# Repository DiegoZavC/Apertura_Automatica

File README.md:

# Apertura_Automatica
 Desarrollo de un sistema de apertura automática para una puera

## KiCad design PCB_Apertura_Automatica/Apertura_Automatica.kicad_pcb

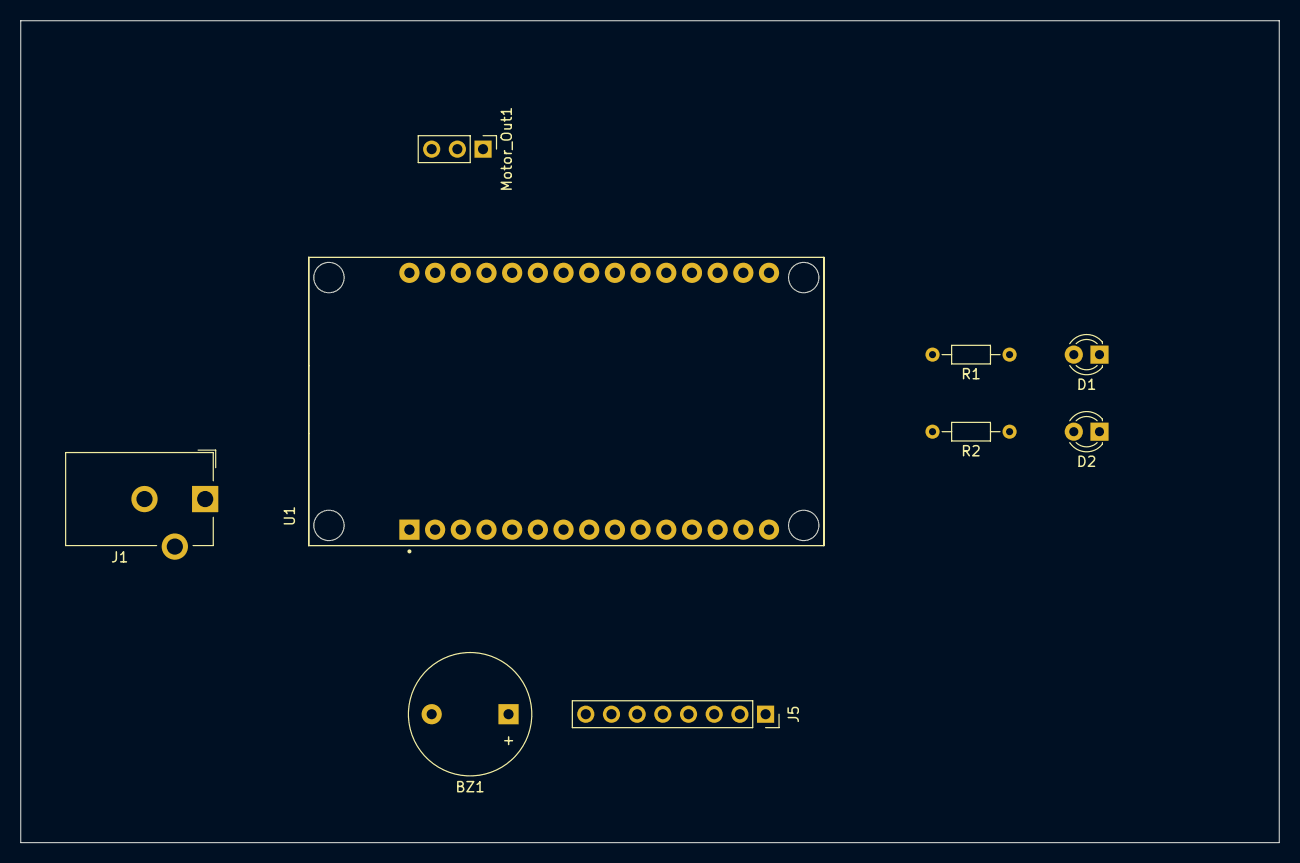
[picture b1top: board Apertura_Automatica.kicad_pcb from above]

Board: 2 copper layers, 124.5 x 81.3 mm, 9 parts (0 on the bottom side), 13 nets, no tracks yet.

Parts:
BZ1: Buzzer; Buzzer_12x9.5RM7.6
D1: LED Verde; LED_D3.0mm
D2: Rojo; LED_D3.0mm
J1: Barrel_Jack_MountingPin; BarrelJack_CUI_PJ-102AH_Horizontal
J5: RFID-RC522; PinSocket_1x08_P2.54mm_Vertical
Motor_Out1: Conn_01x03_Pin; PinHeader_1x03_P2.54mm_Vertical
R1, R2: 330; R_Axial_DIN0204_L3.6mm_D1.6mm_P7.62mm_Horizontal
U1: ESP32-DEVKIT-V1; MODULE_ESP32_DEVKIT_V1

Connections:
GND: BZ1.2 (+), D1.1 (K), D2.1 (K), J1.2, J5.3, Motor_Out1.3, U1.2 (GND), U1.29 (GND)
unnamed: BZ1.1 (-), U1.26 (D14)
unnamed: D1.2 (A), R1.1
unnamed: D2.2 (A), R2.1
unnamed: J5.2, U1.11 (D21)
unnamed: J5.5, U1.10 (D19)
unnamed: J5.6, U1.15 (D23)
unnamed: J5.7, U1.9 (D18)
unnamed: J5.8, U1.8 (D5)
unnamed: Motor_Out1.1, U1.27 (D12)
unnamed: R1.2, U1.23 (D25)
unnamed: R2.2, U1.24 (D26)
VDC: J1.1, Motor_Out1.2, U1.30 (VIN)

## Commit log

2024-04-11 Código y diseño de PCB
